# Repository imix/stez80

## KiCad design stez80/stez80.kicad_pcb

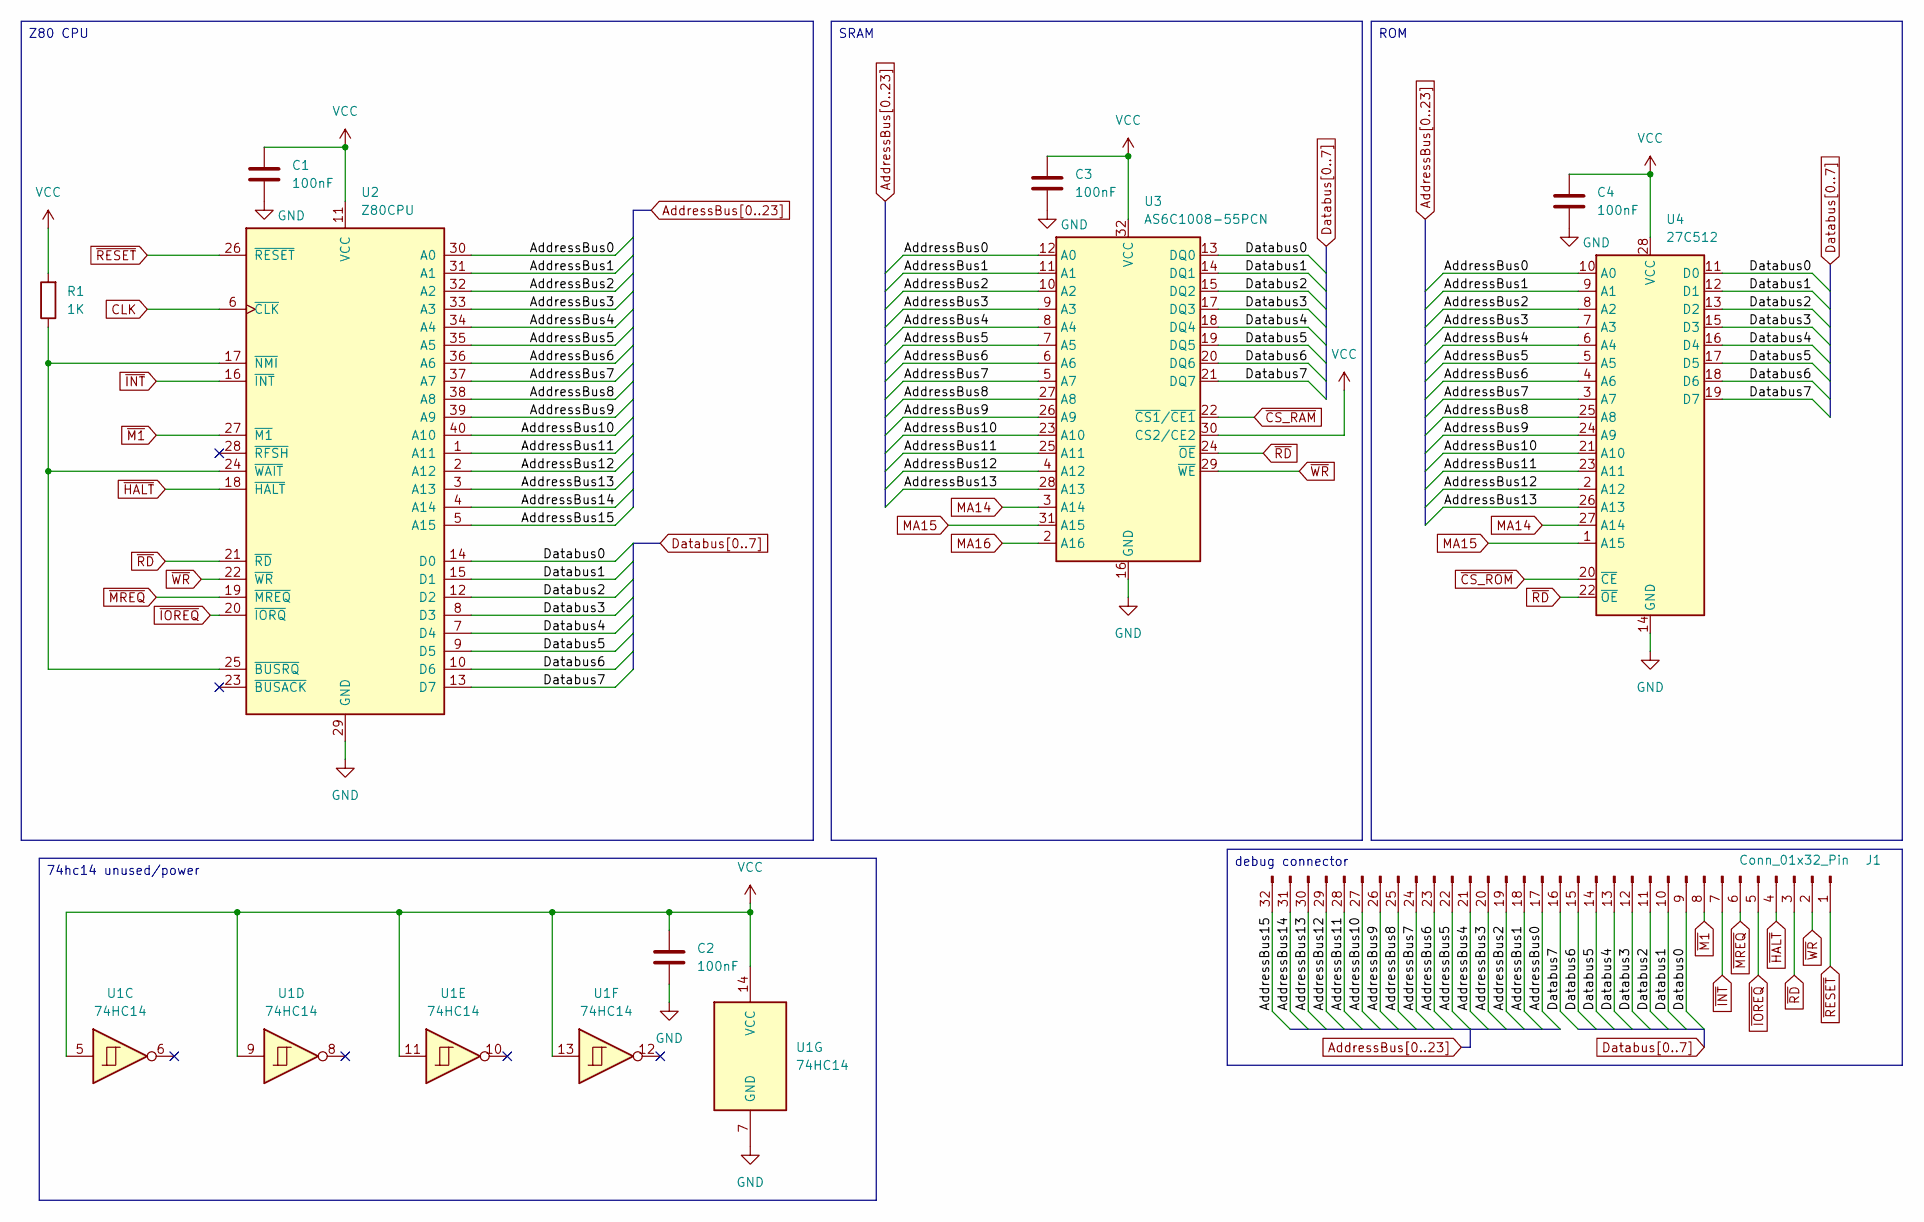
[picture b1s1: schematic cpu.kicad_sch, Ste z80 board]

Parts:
C1, C2, C3, C4: 100nF; C_Rect_L7.0mm_W2.0mm_P5.00mm
J1: Conn_01x32_Pin; PinHeader_1x32_P2.54mm_Vertical
R1: 1K; R_Axial_DIN0207_L6.3mm_D2.5mm_P2.54mm_Vertical
U1: 74HC14; DIP-14_W7.62mm
U2: Z80CPU; DIP-40_W15.24mm_LongPads
U3: AS6C1008-55PCN; DIP-32_W15.24mm_LongPads
U4: 27C512; DIP-28_W15.24mm_LongPads

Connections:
AddressBus0: J1.17, U2.30 (A0), U3.12 (A0), U4.10 (A0); also elsewhere on the board
AddressBus1: J1.18, U2.31 (A1), U3.11 (A1), U4.9 (A1); also elsewhere on the board
AddressBus2: J1.19, U2.32 (A2), U3.10 (A2), U4.8 (A2); also elsewhere on the board
AddressBus3: J1.20, U2.33 (A3), U3.9 (A3), U4.7 (A3); also elsewhere on the board
AddressBus4: J1.21, U2.34 (A4), U3.8 (A4), U4.6 (A4); also elsewhere on the board
AddressBus5: J1.22, U2.35 (A5), U3.7 (A5), U4.5 (A5); also elsewhere on the board
AddressBus6: J1.23, U2.36 (A6), U3.6 (A6), U4.4 (A6); also elsewhere on the board
AddressBus7: J1.24, U2.37 (A7), U3.5 (A7), U4.3 (A7); also elsewhere on the board
AddressBus8: J1.25, U2.38 (A8), U3.27 (A8), U4.25 (A8)
AddressBus9: J1.26, U2.39 (A9), U3.26 (A9), U4.24 (A9)
AddressBus10: J1.27, U2.40 (A10), U3.23 (A10), U4.21 (A10)
AddressBus11: J1.28, U2.1 (A11), U3.25 (A11), U4.23 (A11)
AddressBus12: J1.29, U2.2 (A12), U3.4 (A12), U4.2 (A12)
AddressBus13: J1.30, U2.3 (A13), U3.28 (A13), U4.26 (A13)
AddressBus14: J1.31, U2.4 (A14); also elsewhere on the board
AddressBus15: J1.32, U2.5 (A15); also elsewhere on the board
CLK: U2.6 (~CLK); also elsewhere on the board
Databus0: J1.9, U2.14 (D0), U3.13 (DQ0), U4.11 (D0); also elsewhere on the board
Databus1: J1.10, U2.15 (D1), U3.14 (DQ1), U4.12 (D1); also elsewhere on the board
Databus2: J1.11, U2.12 (D2), U3.15 (DQ2), U4.13 (D2); also elsewhere on the board
Databus3: J1.12, U2.8 (D3), U3.17 (DQ3), U4.15 (D3); also elsewhere on the board
Databus4: J1.13, U2.7 (D4), U3.18 (DQ4), U4.16 (D4); also elsewhere on the board
Databus5: J1.14, U2.9 (D5), U3.19 (DQ5), U4.17 (D5); also elsewhere on the board
Databus6: J1.15, U2.10 (D6), U3.20 (DQ6), U4.18 (D6); also elsewhere on the board
Databus7: J1.16, U2.13 (D7), U3.21 (DQ7), U4.19 (D7); also elsewhere on the board
GND: C1.2, C2.2, C3.2, C4.2, U1.7 (GND), U2.29 (GND), U3.16 (GND), U4.14 (GND); also elsewhere on the board
MA14: U3.3 (A14), U4.27 (A14); also elsewhere on the board
MA15: U3.31 (A15), U4.1 (A15); also elsewhere on the board
MA16: U3.2 (A16); also elsewhere on the board
unnamed: R1.1, U2.17 (~NMI), U2.24 (~WAIT), U2.25 (~BUSRQ)
VCC: C1.1, C2.1, C3.1, C4.1, R1.2, U1.5, U1.9, U1.11, U1.13, U1.14 (VCC), U2.11 (VCC), U3.30 (CS2/CE2), U3.32 (VCC), U4.28 (VCC); also elsewhere on the board
~CS_RAM: U3.22 (~CS1/~CE1); also elsewhere on the board
~CS_ROM: U4.20 (~CE); also elsewhere on the board
~HALT: J1.4, U2.18 (~HALT); also elsewhere on the board
~INT: J1.7, U2.16 (~INT); also elsewhere on the board
~IOREQ: J1.5, U2.20 (~IORQ); also elsewhere on the board
~M1: J1.8, U2.27 (~M1); also elsewhere on the board
~MREQ: J1.6, U2.19 (~MREQ); also elsewhere on the board
~RD: J1.3, U2.21 (~RD), U3.24 (~OE), U4.22 (~OE); also elsewhere on the board
~RESET: J1.1, U2.26 (~RESET); also elsewhere on the board
~WR: J1.2, U2.22 (~WR), U3.29 (~WE); also elsewhere on the board

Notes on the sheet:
74hc14 unused/power
ROM
SRAM
Z80 CPU
debug connector

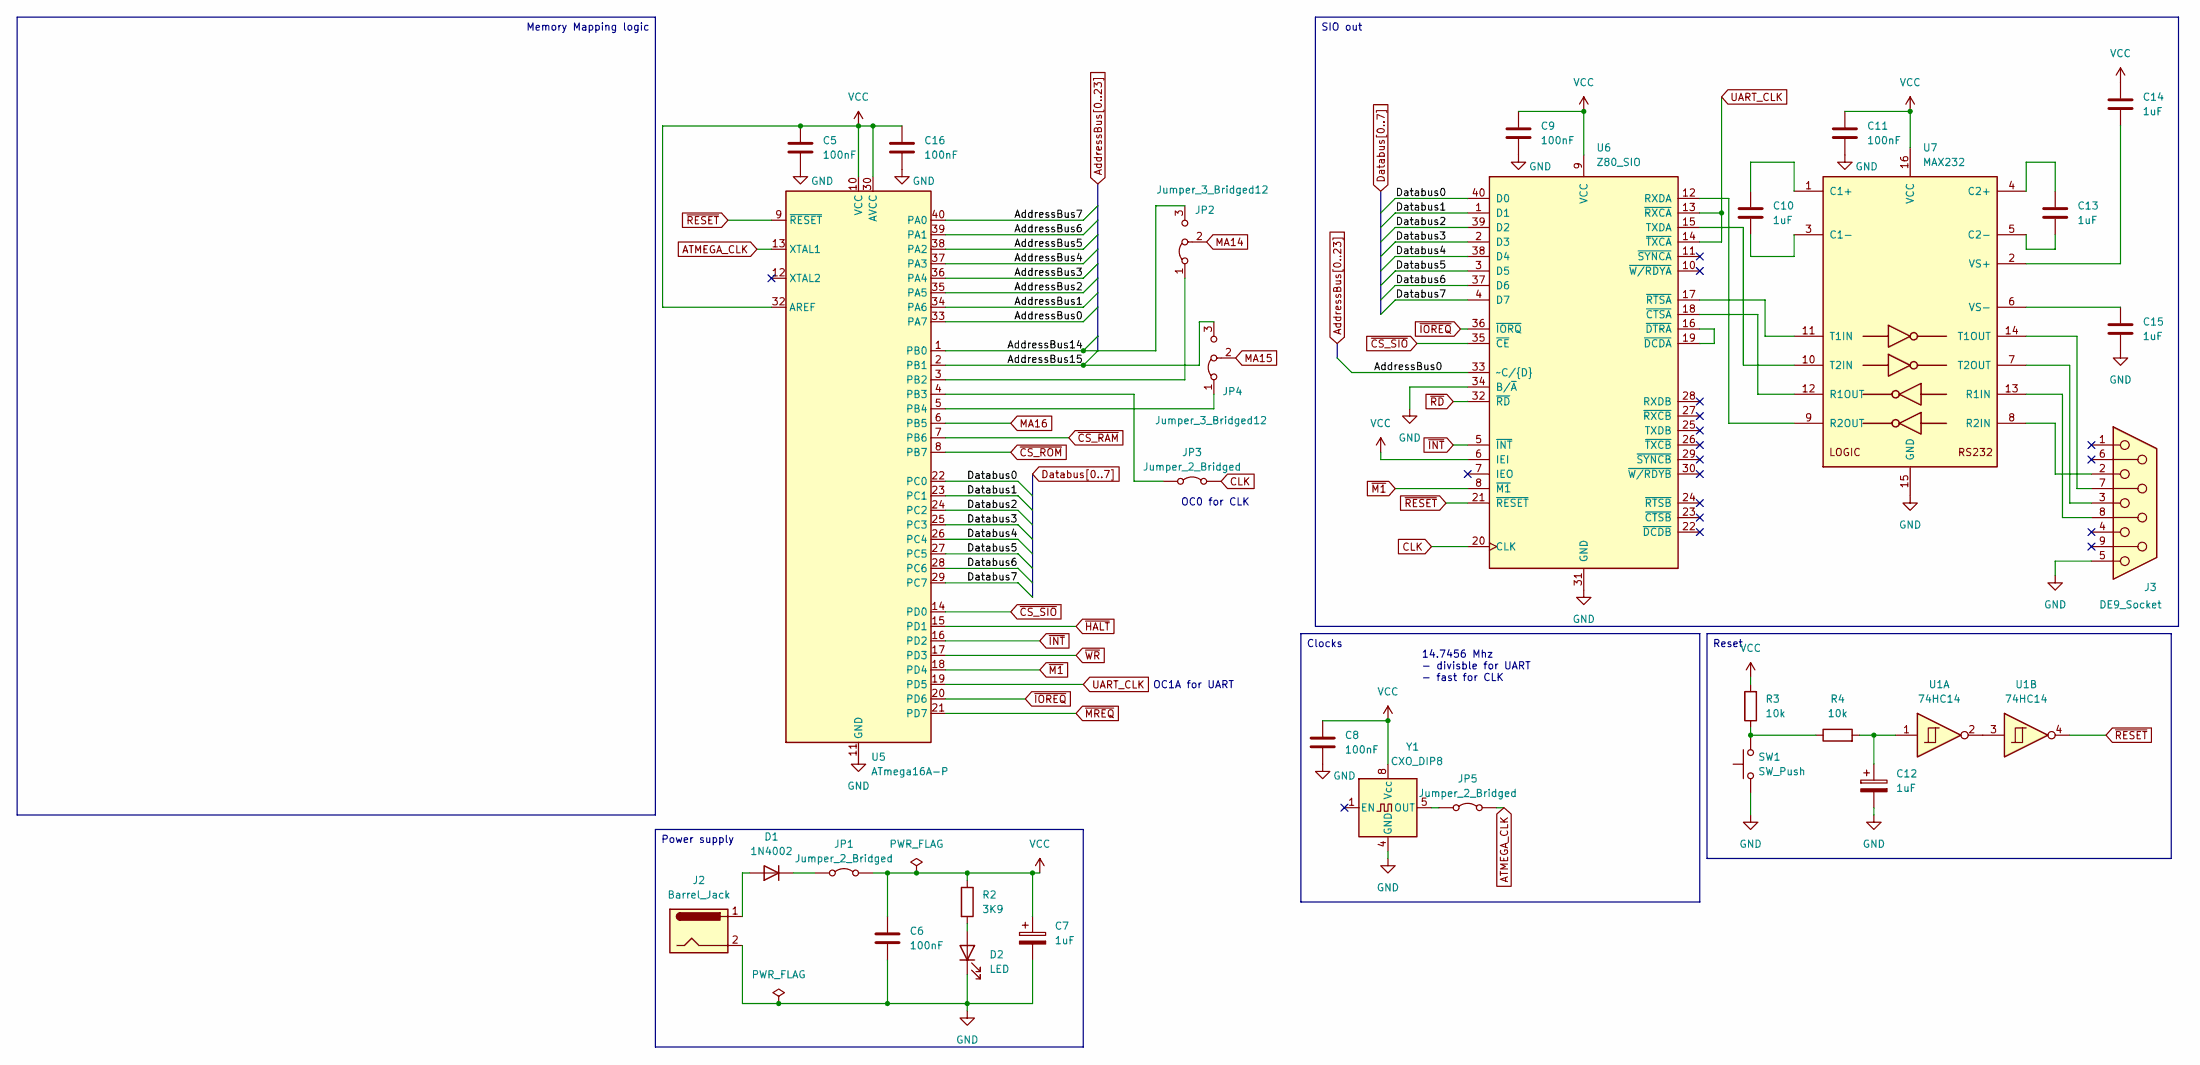
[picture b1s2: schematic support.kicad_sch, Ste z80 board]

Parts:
C5, C6, C8, C9, C11, C16: 100nF; C_Rect_L7.0mm_W2.0mm_P5.00mm
C7, C12: 1uF; CP_Radial_D5.0mm_P2.50mm
C10, C13, C14, C15: 1uF; C_Rect_L7.0mm_W2.0mm_P5.00mm
D1: 1N4002; D_DO-15_P15.24mm_Horizontal
D2: LED; LED_D3.0mm_Clear
J2: Barrel_Jack; BarrelJack_GCT_DCJ200-10-A_Horizontal
J3: DE9_Socket; DSUB-9_Socket_Horizontal_P2.77x2.84mm_EdgePinOffset7.70mm_H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
JP1, JP3, JP5: Jumper_2_Bridged; PinHeader_1x02_P2.54mm_Vertical
JP2, JP4: Jumper_3_Bridged12; PinHeader_1x03_P2.54mm_Vertical
R2: 3K9; R_Axial_DIN0207_L6.3mm_D2.5mm_P2.54mm_Vertical
R3, R4: 10k; R_Axial_DIN0207_L6.3mm_D2.5mm_P2.54mm_Vertical
SW1: SW_Push; SW_PUSH_6mm_H7.3mm
U1: 74HC14; DIP-14_W7.62mm
U5: ATmega16A-P; DIP-40_W15.24mm_LongPads
U6: Z80_SIO; DIP-40_W15.24mm_LongPads
U7: MAX232; DIP-16_W7.62mm_LongPads
Y1: CXO_DIP8; Oscillator_DIP-8

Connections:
ATMEGA_CLK: JP5.2 (B), U5.13 (XTAL1)
AddressBus0: U5.33 (PA7), U6.33 (~C/{D}); also elsewhere on the board
AddressBus1: U5.34 (PA6); also elsewhere on the board
AddressBus2: U5.35 (PA5); also elsewhere on the board
AddressBus3: U5.36 (PA4); also elsewhere on the board
AddressBus4: U5.37 (PA3); also elsewhere on the board
AddressBus5: U5.38 (PA2); also elsewhere on the board
AddressBus6: U5.39 (PA1); also elsewhere on the board
AddressBus7: U5.40 (PA0); also elsewhere on the board
AddressBus14: JP2.3 (B), U5.1 (PB0); also elsewhere on the board
AddressBus15: JP4.3 (B), U5.2 (PB1); also elsewhere on the board
CLK: JP3.2 (B), U6.20 (CLK); also elsewhere on the board
Databus0: U5.22 (PC0), U6.40 (D0); also elsewhere on the board
Databus1: U5.23 (PC1), U6.1 (D1); also elsewhere on the board
Databus2: U5.24 (PC2), U6.39 (D2); also elsewhere on the board
Databus3: U5.25 (PC3), U6.2 (D3); also elsewhere on the board
Databus4: U5.26 (PC4), U6.38 (D4); also elsewhere on the board
Databus5: U5.27 (PC5), U6.3 (D5); also elsewhere on the board
Databus6: U5.28 (PC6), U6.37 (D6); also elsewhere on the board
Databus7: U5.29 (PC7), U6.4 (D7); also elsewhere on the board
GND: C5.2, C6.2, C7.2, C8.2, C9.2, C11.2, C12.2, C15.2, C16.2, D2.1 (K), J2.2, J3.5, SW1.1, U5.11 (GND), U5.31 (GND), U6.31 (GND), U6.34 (B/~A), U7.15 (GND), Y1.4 (GND); also elsewhere on the board
MA14: JP2.2 (C); also elsewhere on the board
MA15: JP4.2 (C); also elsewhere on the board
MA16: U5.6 (PB5); also elsewhere on the board
unnamed: C12.1, R4.2, U1.1
unnamed: D1.2 (A), J2.1
unnamed: D1.1 (K), JP1.1 (A)
unnamed: D2.2 (A), R2.2
unnamed: JP2.1 (A), U5.3 (PB2)
unnamed: JP3.1 (A), U5.4 (PB3)
unnamed: JP4.1 (A), U5.5 (PB4)
unnamed: JP5.1 (A), Y1.5 (OUT)
unnamed: R3.1, R4.1, SW1.2
unnamed: U1.2, U1.3
unnamed: U6.12 (RXDA), U7.9 (R2OUT)
unnamed: U6.15 (TXDA), U7.10 (T2IN)
unnamed: U6.18 (~CTSA), U7.12 (R1OUT)
unnamed: U6.16 (~DTRA), U6.19 (~DCDA)
unnamed: U6.17 (~RTSA), U7.11 (T1IN)
unnamed: C10.1, U7.1 (C1+)
unnamed: C10.2, U7.3 (C1-)
unnamed: C13.1, U7.4 (C2+)
unnamed: C13.2, U7.5 (C2-)
unnamed: J3.8, U7.13 (R1IN)
unnamed: J3.2, U7.8 (R2IN)
unnamed: J3.7, U7.14 (T1OUT)
unnamed: J3.3, U7.7 (T2OUT)
unnamed: C14.2, U7.2 (VS+)
unnamed: C15.1, U7.6 (VS-)
UART_CLK: U5.19 (PD5), U6.13 (~RXCA), U6.14 (~TXCA)
VCC: C5.1, C6.1, C7.1, C8.1, C9.1, C11.1, C14.1, C16.1, JP1.2 (B), R2.1, R3.2, U5.10 (VCC), U5.30 (AVCC), U5.32 (AREF), U6.6 (IEI), U6.9 (VCC), U7.16 (VCC), Y1.8 (Vcc); also elsewhere on the board
~CS_RAM: U5.7 (PB6); also elsewhere on the board
~CS_ROM: U5.8 (PB7); also elsewhere on the board
~CS_SIO: U5.14 (PD0), U6.35 (~CE)
~HALT: U5.15 (PD1); also elsewhere on the board
~INT: U5.16 (PD2), U6.5 (~INT); also elsewhere on the board
~IOREQ: U5.20 (PD6), U6.36 (~IORQ); also elsewhere on the board
~M1: U5.18 (PD4), U6.8 (~M1); also elsewhere on the board
~MREQ: U5.21 (PD7); also elsewhere on the board
~RD: U6.32 (~RD); also elsewhere on the board
~RESET: U1.4, U5.9 (~RESET), U6.21 (~RESET); also elsewhere on the board
~WR: U5.17 (PD3); also elsewhere on the board

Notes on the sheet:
OC0 for CLK
14.7456 Mhz - divisble for UART - fast for CLK
OC1A for UART
SIO out
Power supply
Reset
Memory Mapping logic
Clocks

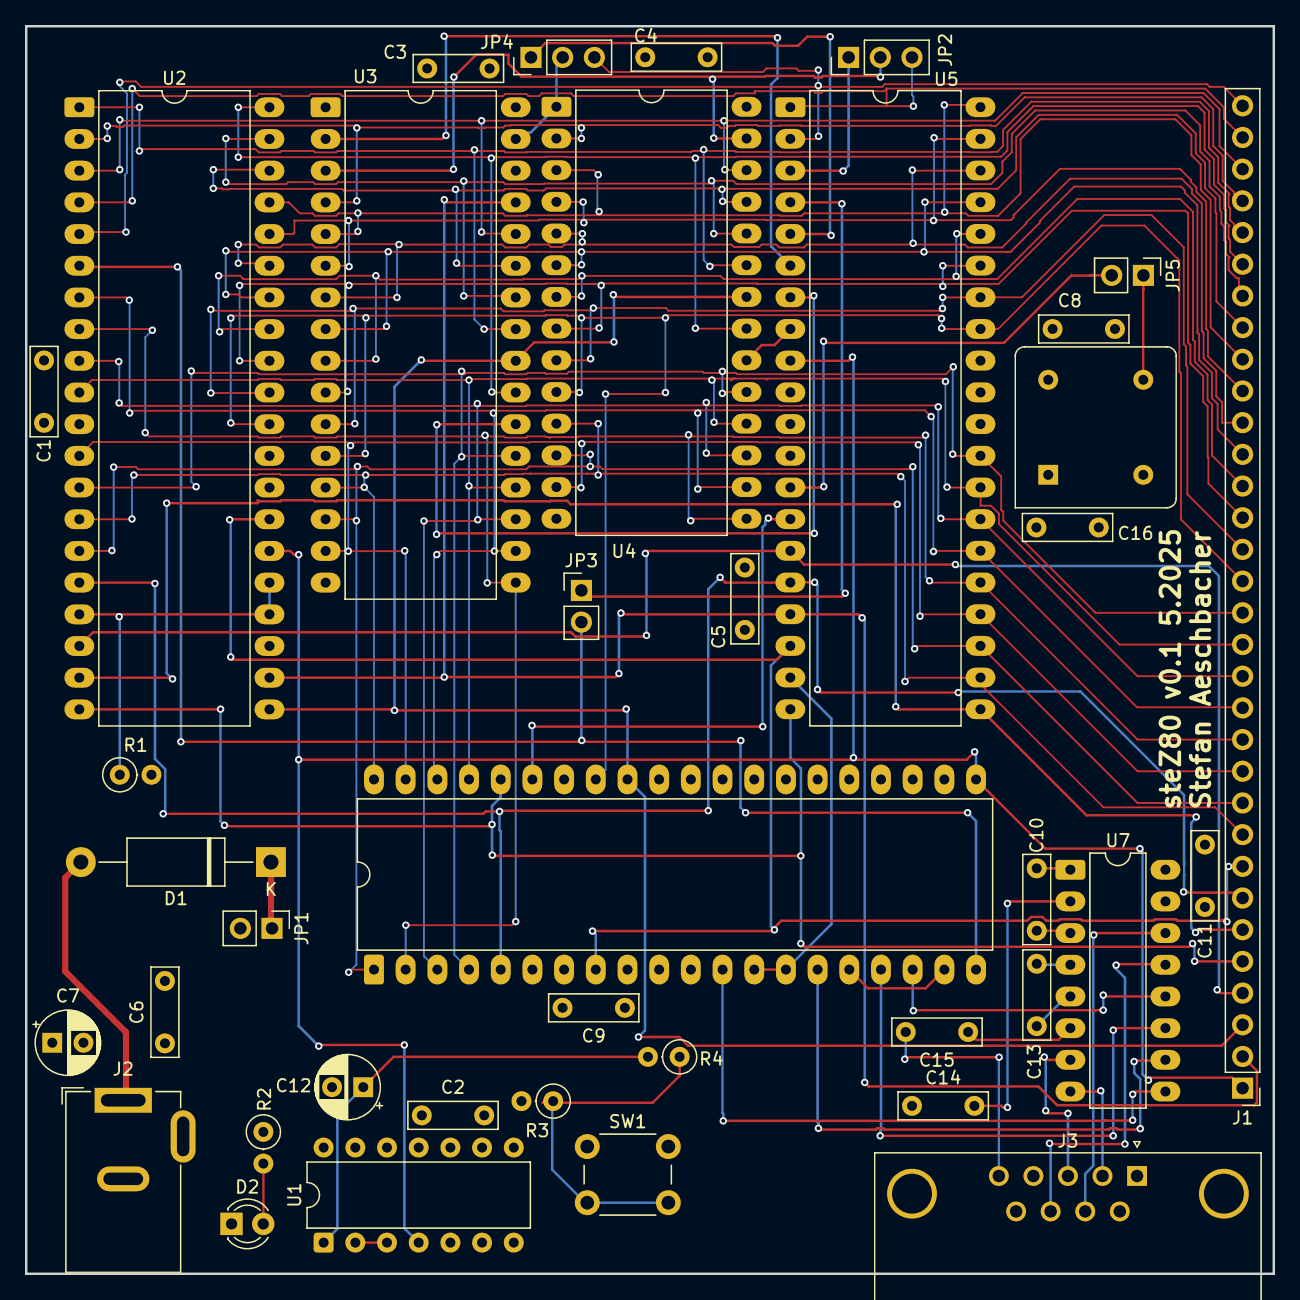
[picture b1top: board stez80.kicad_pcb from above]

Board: 4 copper layers, 100.0 x 100.0 mm, 39 parts (0 on the bottom side), 69 nets.

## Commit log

2025-04-27 initial import
2025-04-27 initial import schematics
2025-04-27 asm build script
2025-04-27 use z88dk from docker
2025-04-27 add constants, rename emulator folder
2025-05-10 pcb layout
2025-05-13 review wip
2025-05-17 continue review
2025-05-18 v0.1
